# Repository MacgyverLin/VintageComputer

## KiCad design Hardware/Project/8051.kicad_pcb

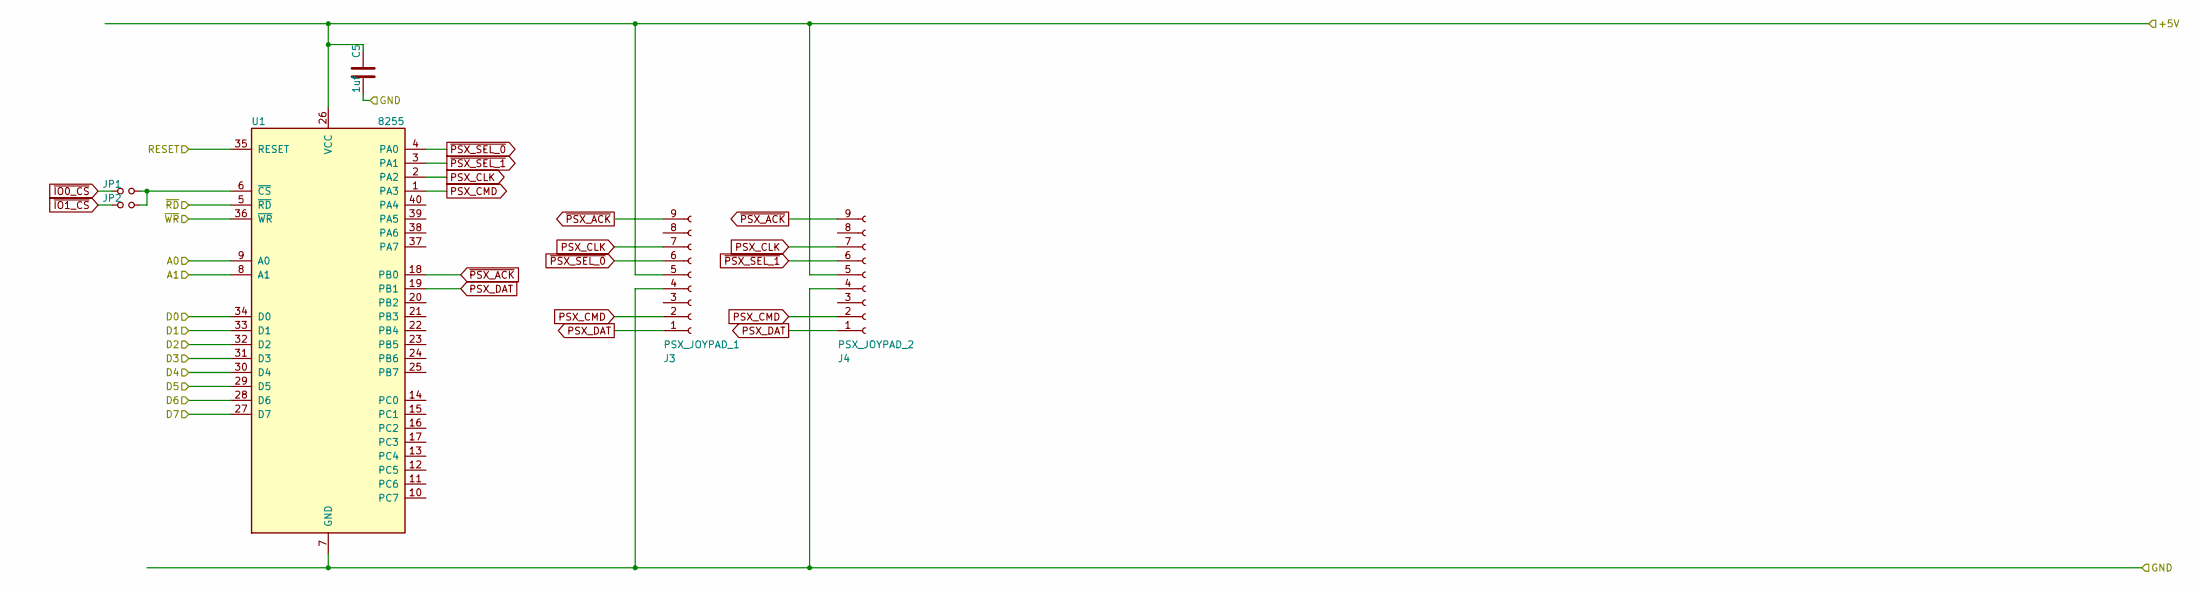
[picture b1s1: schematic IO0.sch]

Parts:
C5: 1uf; C_0805_2012Metric
J3: PSX_JOYPAD_1; PinSocket_1x09_P2.54mm_Vertical
J4: PSX_JOYPAD_2; PinSocket_1x09_P2.54mm_Vertical
JP1, JP2: SolderJumper-2_P1.3mm_Open_RoundedPad1.0x1.5mm
U1: 8255; DIP-40_W15.24mm

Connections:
/+5V: C5.1, J3.5, J4.5, U1.26 (VCC); also elsewhere on the board
/GND: C5.2, J3.4, J4.4, U1.7 (GND); also elsewhere on the board
/RESET: U1.35 (RESET); also elsewhere on the board
/~A0: U1.9 (A0); also elsewhere on the board
/~A1: U1.8 (A1); also elsewhere on the board
/~D0: U1.34 (D0); also elsewhere on the board
/~D1: U1.33 (D1); also elsewhere on the board
/~D2: U1.32 (D2); also elsewhere on the board
/~D3: U1.31 (D3); also elsewhere on the board
/~D4: U1.30 (D4); also elsewhere on the board
/~D5: U1.29 (D5); also elsewhere on the board
/~D6: U1.28 (D6); also elsewhere on the board
/~D7: U1.27 (D7); also elsewhere on the board
/~RD: U1.5 (~RD~); also elsewhere on the board
/~WR: U1.36 (~WR~); also elsewhere on the board
unnamed: JP1.2, JP2.2, U1.6 (~CS~)
PSX_CLK: J3.7, J4.7, U1.2 (PA2)
PSX_CMD: J3.2, J4.2, U1.1 (PA3)
PSX_DAT: J3.1, J4.1, U1.19 (PB1)
~IO0_CS: JP1.1; also elsewhere on the board
~IO1_CS: JP2.1; also elsewhere on the board
~PSX_ACK: J3.9, J4.9, U1.18 (PB0)
~PSX_SEL_0: J3.6, U1.4 (PA0)
~PSX_SEL_1: J4.6, U1.3 (PA1)

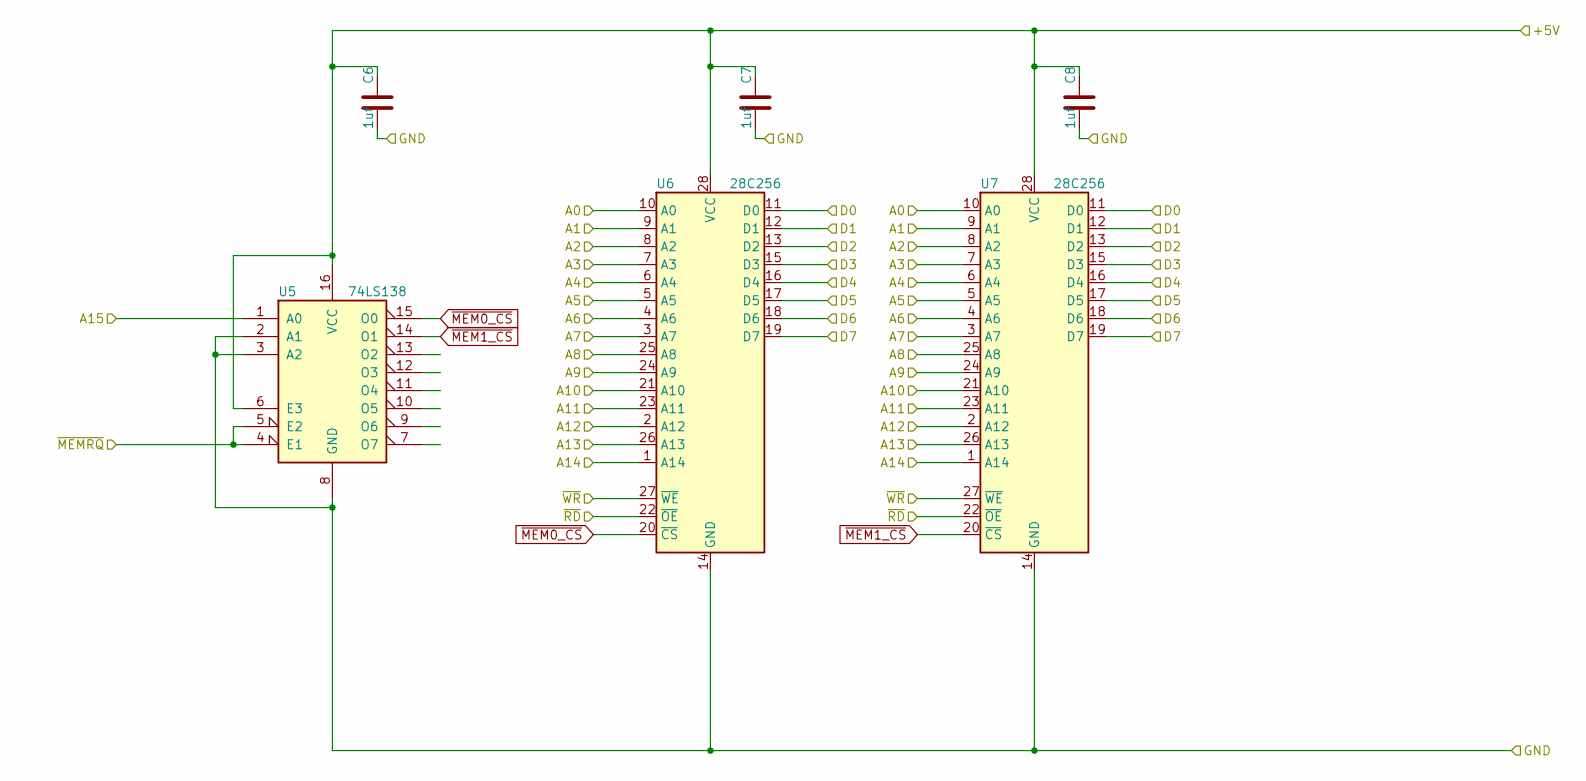
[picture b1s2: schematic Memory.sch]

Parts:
C6, C7, C8: 1uf; C_0805_2012Metric
U5: 74LS138; DIP-16_W7.62mm_Socket
U6, U7: 28C256; DIP-28_W15.24mm_Socket

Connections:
/+5V: C6.1, C7.1, C8.1, U5.6 (E3), U5.16 (VCC), U6.28 (VCC), U7.28 (VCC); also elsewhere on the board
/GND: C6.2, C7.2, C8.2, U5.2 (A1), U5.3 (A2), U5.8 (GND), U6.14 (GND), U7.14 (GND); also elsewhere on the board
/~A0: U6.10 (A0), U7.10 (A0); also elsewhere on the board
/~A1: U6.9 (A1), U7.9 (A1); also elsewhere on the board
/~A2: U6.8 (A2), U7.8 (A2); also elsewhere on the board
/~A3: U6.7 (A3), U7.7 (A3); also elsewhere on the board
/~A4: U6.6 (A4), U7.6 (A4); also elsewhere on the board
/~A5: U6.5 (A5), U7.5 (A5); also elsewhere on the board
/~A6: U6.4 (A6), U7.4 (A6); also elsewhere on the board
/~A7: U6.3 (A7), U7.3 (A7); also elsewhere on the board
/~A8: U6.25 (A8), U7.25 (A8); also elsewhere on the board
/~A9: U6.24 (A9), U7.24 (A9); also elsewhere on the board
/~A10: U6.21 (A10), U7.21 (A10); also elsewhere on the board
/~A11: U6.23 (A11), U7.23 (A11); also elsewhere on the board
/~A12: U6.2 (A12), U7.2 (A12); also elsewhere on the board
/~A13: U6.26 (A13), U7.26 (A13); also elsewhere on the board
/~A14: U6.1 (A14), U7.1 (A14); also elsewhere on the board
/~A15: U5.1 (A0); also elsewhere on the board
/~D0: U6.11 (D0), U7.11 (D0); also elsewhere on the board
/~D1: U6.12 (D1), U7.12 (D1); also elsewhere on the board
/~D2: U6.13 (D2), U7.13 (D2); also elsewhere on the board
/~D3: U6.15 (D3), U7.15 (D3); also elsewhere on the board
/~D4: U6.16 (D4), U7.16 (D4); also elsewhere on the board
/~D5: U6.17 (D5), U7.17 (D5); also elsewhere on the board
/~D6: U6.18 (D6), U7.18 (D6); also elsewhere on the board
/~D7: U6.19 (D7), U7.19 (D7); also elsewhere on the board
/~MEMRQ: U5.4 (E1), U5.5 (E2); also elsewhere on the board
/~RD: U6.22 (~OE), U7.22 (~OE); also elsewhere on the board
/~WR: U6.27 (~WE), U7.27 (~WE); also elsewhere on the board
~MEM0_CS: U5.15 (O0), U6.20 (~CS)
~MEM1_CS: U5.14 (O1), U7.20 (~CS)

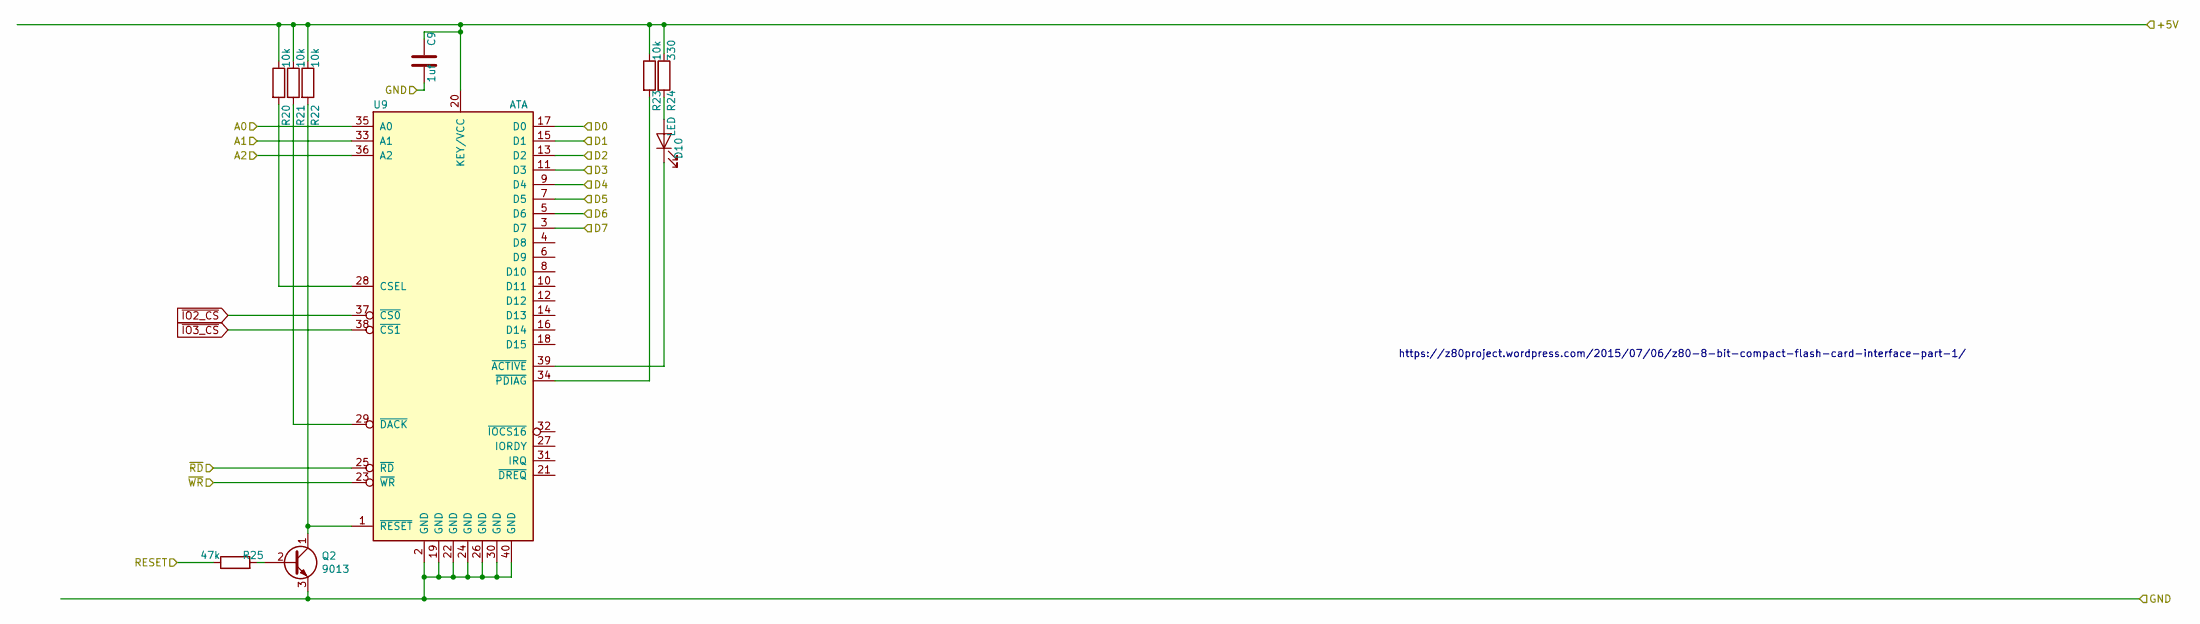
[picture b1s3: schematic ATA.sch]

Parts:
C9: 1uf; C_0805_2012Metric
D10: LED; LED_0805_2012Metric
Q2: 9013; TO-92
R20, R21, R22, R23: 10k; R_0805_2012Metric
R24: 330; R_0805_2012Metric
R25: 47k; R_0805_2012Metric
U9: ATA; PinHeader_2x20_P2.54mm_Vertical

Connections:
/+5V: C9.1, R20.1, R21.1, R22.1, R23.1, R24.1, U9.20 (KEY/VCC); also elsewhere on the board
/GND: C9.2, Q2.3 (E), U9.2 (GND), U9.19 (GND), U9.22 (GND), U9.24 (GND), U9.26 (GND), U9.30 (GND), U9.40 (GND); also elsewhere on the board
/RESET: R25.1; also elsewhere on the board
/~A0: U9.35 (A0); also elsewhere on the board
/~A1: U9.33 (A1); also elsewhere on the board
/~A2: U9.36 (A2); also elsewhere on the board
/~D0: U9.17 (D0); also elsewhere on the board
/~D1: U9.15 (D1); also elsewhere on the board
/~D2: U9.13 (D2); also elsewhere on the board
/~D3: U9.11 (D3); also elsewhere on the board
/~D4: U9.9 (D4); also elsewhere on the board
/~D5: U9.7 (D5); also elsewhere on the board
/~D6: U9.5 (D6); also elsewhere on the board
/~D7: U9.3 (D7); also elsewhere on the board
/~RD: U9.25 (~RD); also elsewhere on the board
/~WR: U9.23 (~WR); also elsewhere on the board
unnamed: D10.1 (K), U9.39 (~ACTIVE)
unnamed: D10.2 (A), R24.2
unnamed: Q2.1 (C), R22.2, U9.1 (~RESET~)
unnamed: Q2.2 (B), R25.2
unnamed: R20.2, U9.28 (CSEL)
unnamed: R21.2, U9.29 (~DACK)
unnamed: R23.2, U9.34 (~PDIAG)
~IO2_CS: U9.37 (~CS0); also elsewhere on the board
~IO3_CS: U9.38 (~CS1); also elsewhere on the board

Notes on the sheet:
https://z80project.wordpress.com/2015/07/06/z80-8-bit-compact-flash-card-interface-part-1/

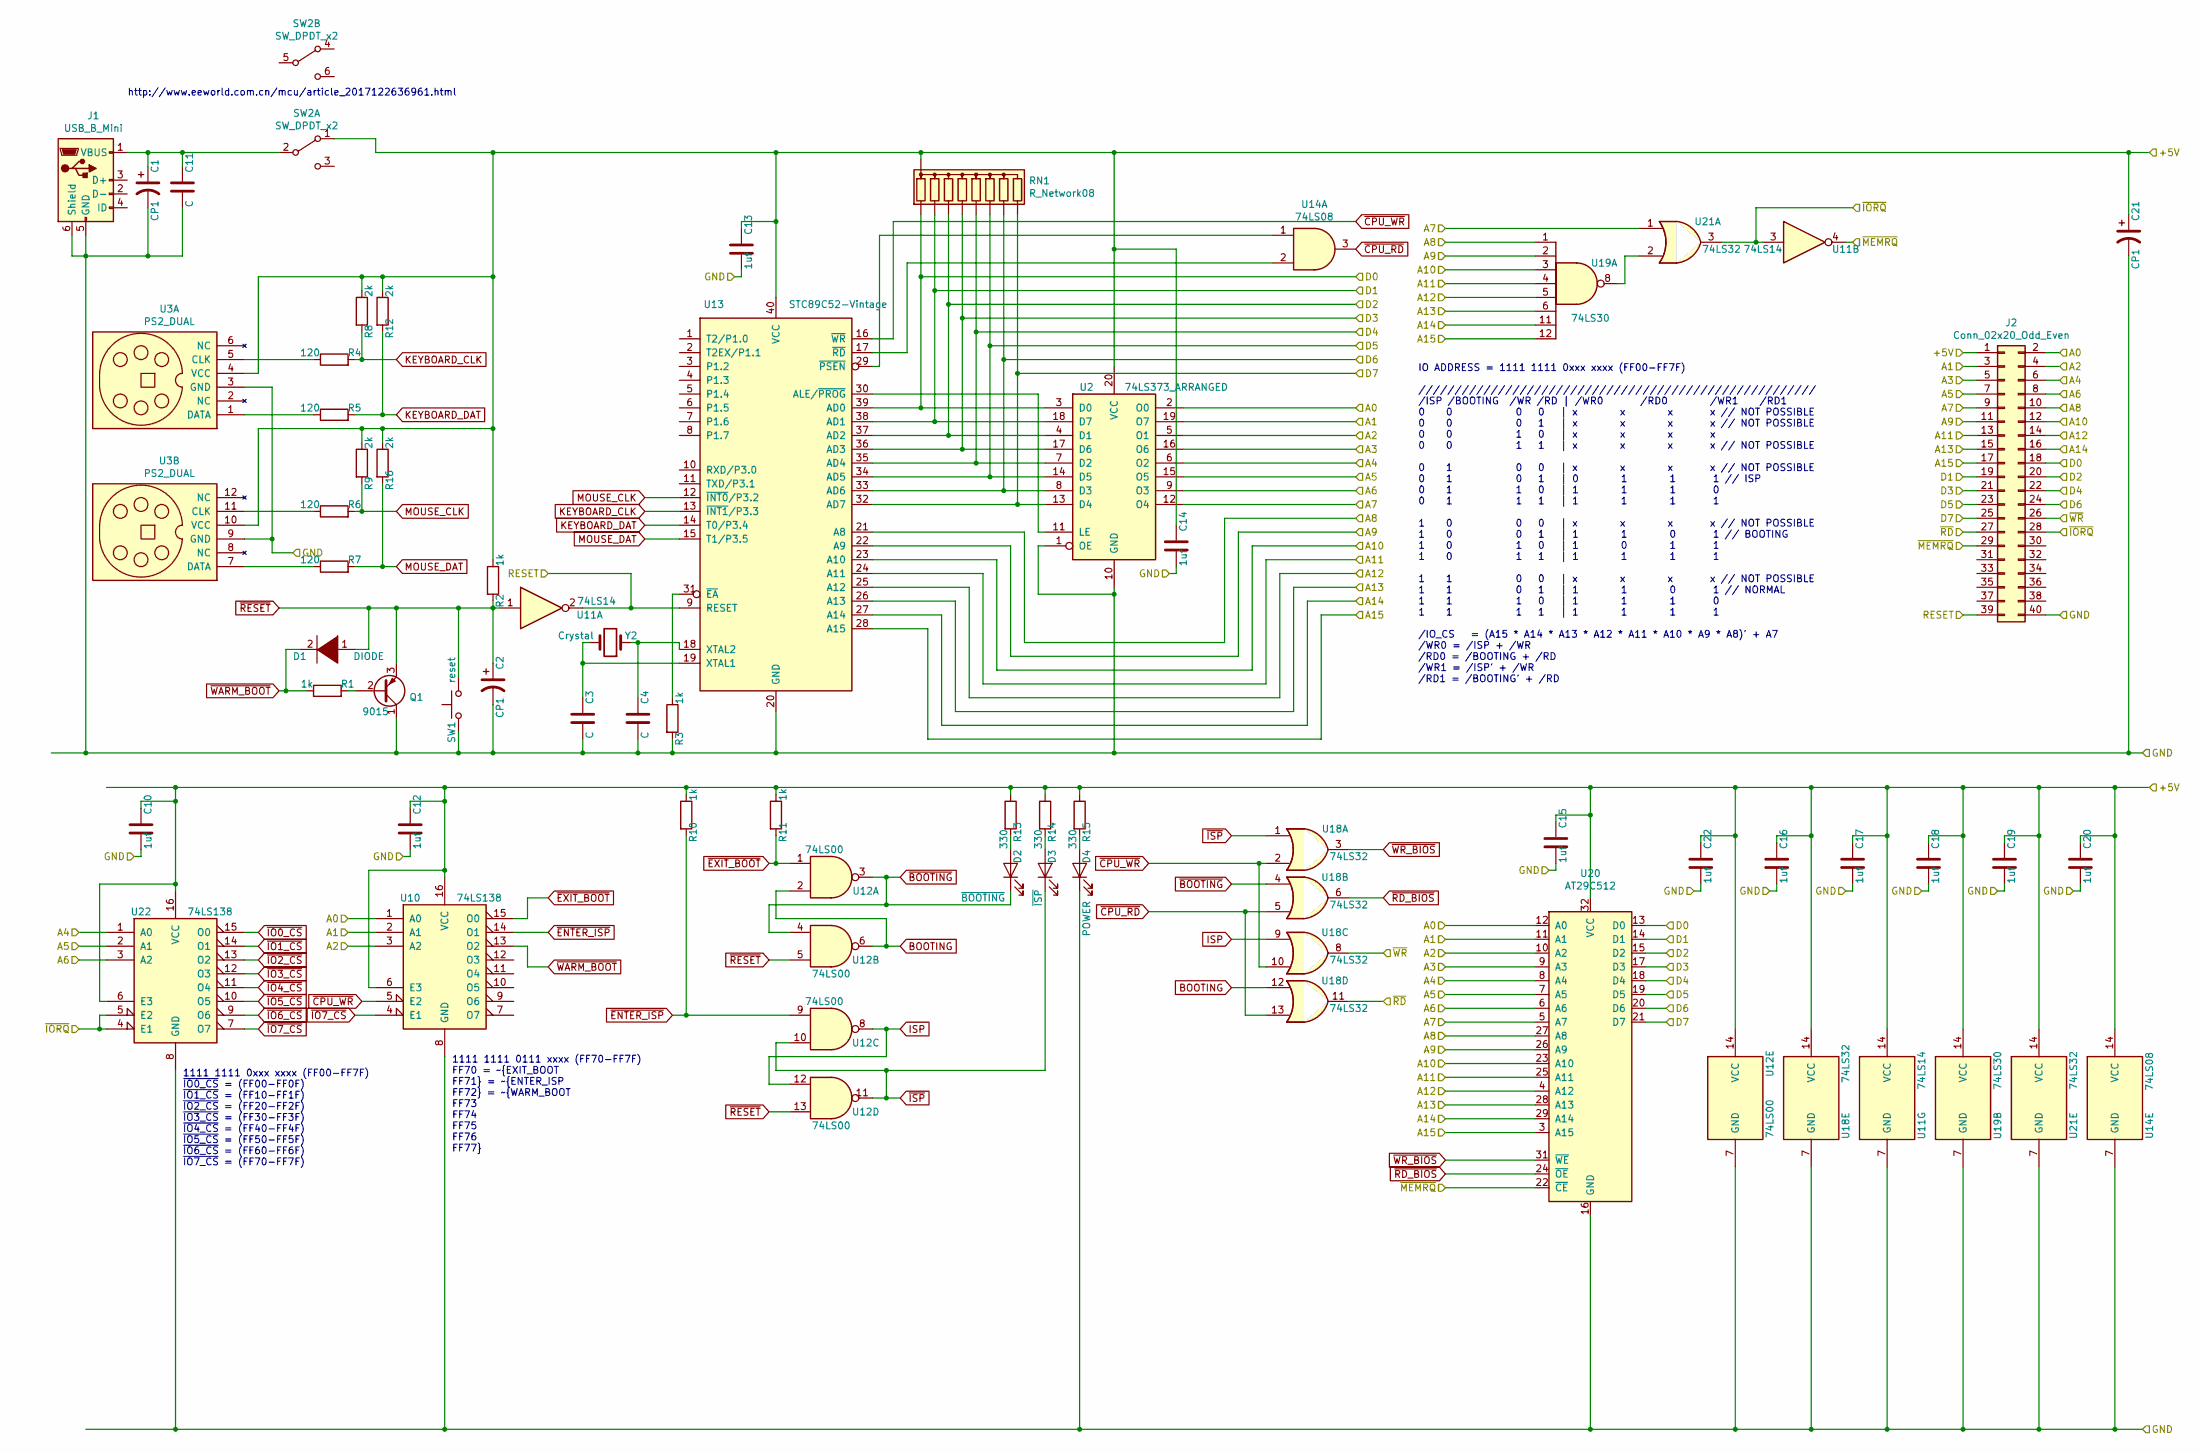
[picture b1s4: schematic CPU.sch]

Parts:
C1, C2, C21: CP1; CP_Radial_D7.5mm_P2.50mm
C3, C4, C11: C; C_0805_2012Metric
C10, C12, C13, C14, C15, C16, C17, C18, C19, C20, C22: 1uf; C_0805_2012Metric
D1: DIODE; LED_0805_2012Metric
D2: ~BOOTING; LED_0805_2012Metric
D3: ~ISP; LED_0805_2012Metric
D4: POWER; LED_0805_2012Metric
J1: USB_B_Mini; USB_Micro-B_Wuerth_629105150521_CircularHoles
J2: Conn_02x20_Odd_Even; PinHeader_2x20_P2.54mm_Vertical
Q1: 9015; TO-92
R1, R2, R3, R10, R11: 1k; R_0805_2012Metric
R4, R5, R6, R7: 120; R_0805_2012Metric
R8, R9, R12, R16: 2k; R_0805_2012Metric
R13, R14, R15: 330; R_0805_2012Metric
RN1: R_Network08; R_Array_SIP9
SW1: reset; SW_PUSH_6mm
SW2: SW_DPDT_x2; DIP-6_W7.62mm
U2: 74LS373_ARRANGED; DIP-20_W7.62mm_Socket
U3: PS2_DUAL; PS2DUAL
U10, U22: 74LS138; DIP-16_W7.62mm_Socket
U11: 74LS14; DIP-14_W7.62mm_Socket
U12: 74LS00; DIP-14_W7.62mm_Socket
U13: STC89C52-Vintage; DIP-40_W15.24mm_Socket
U14: 74LS08; DIP-14_W7.62mm_Socket
U18, U21: 74LS32; DIP-14_W7.62mm_Socket
U19: 74LS30; DIP-14_W7.62mm_Socket
U20: AT29C512; DIP-32_W15.24mm_Socket
Y2: Crystal; Crystal_HC18-U_Vertical

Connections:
/+5V: C10.1, C12.1, C13.1, C14.1, C15.1, C16.1, C17.1, C18.1, C19.1, C20.1, C21.1, C22.1, J2.1, R2.1, R8.1, R9.1, R10.1, R11.1, R12.1, R13.1, R14.1, R15.1, R16.1, RN1.1 (common), SW2.1 (A), U2.20 (VCC), U3.4 (VCC), U3.10 (VCC), U10.6 (E3), U10.16 (VCC), U11.14 (VCC), U12.14 (VCC), U13.40 (VCC), U14.14 (VCC), U18.14 (VCC), U19.14 (VCC), U20.32 (VCC), U21.14 (VCC), U22.6 (E3), U22.16 (VCC); also elsewhere on the board
/GND: C1.2, C2.2, C3.2, C4.2, C10.2, C11.2, C12.2, C13.2, C14.2, C15.2, C16.2, C17.2, C18.2, C19.2, C20.2, C21.2, C22.2, D4.1 (K), J1.5 (GND), J1.6 (Shield), J2.40, Q1.1 (C), R3.2, SW1.1, U2.1 (OE), U2.10 (GND), U3.3 (GND), U3.9 (GND), U10.8 (GND), U11.7 (GND), U12.7 (GND), U13.20 (GND), U14.7 (GND), U18.7 (GND), U19.7 (GND), U20.16 (GND), U21.7 (GND), U22.8 (GND); also elsewhere on the board
/RESET: J2.39, U11.2, U13.9 (RESET); also elsewhere on the board
/~A0: J2.2, U2.2 (O0), U10.1 (A0), U20.12 (A0); also elsewhere on the board
/~A1: J2.3, U2.19 (O7), U10.2 (A1), U20.11 (A1); also elsewhere on the board
/~A2: J2.4, U2.5 (O1), U10.3 (A2), U20.10 (A2); also elsewhere on the board
/~A3: J2.5, U2.16 (O6), U20.9 (A3); also elsewhere on the board
/~A4: J2.6, U2.6 (O2), U20.8 (A4), U22.1 (A0); also elsewhere on the board
/~A5: J2.7, U2.15 (O5), U20.7 (A5), U22.2 (A1); also elsewhere on the board
/~A6: J2.8, U2.9 (O3), U20.6 (A6), U22.3 (A2); also elsewhere on the board
/~A7: J2.9, U2.12 (O4), U20.5 (A7), U21.1; also elsewhere on the board
/~A8: J2.10, U13.21 (A8), U19.1, U20.27 (A8); also elsewhere on the board
/~A9: J2.11, U13.22 (A9), U19.2, U20.26 (A9); also elsewhere on the board
/~A10: J2.12, U13.23 (A10), U19.3, U20.23 (A10); also elsewhere on the board
/~A11: J2.13, U13.24 (A11), U19.4, U20.25 (A11); also elsewhere on the board
/~A12: J2.14, U13.25 (A12), U19.5, U20.4 (A12); also elsewhere on the board
/~A13: J2.15, U13.26 (A13), U19.6, U20.28 (A13); also elsewhere on the board
/~A14: J2.16, U13.27 (A14), U19.11, U20.29 (A14); also elsewhere on the board
/~A15: J2.17, U13.28 (A15), U19.12, U20.3 (A15); also elsewhere on the board
/~D0: J2.18, RN1.2 (R1), U2.3 (D0), U13.39 (AD0), U20.13 (D0); also elsewhere on the board
/~D1: J2.19, RN1.3 (R2), U2.18 (D7), U13.38 (AD1), U20.14 (D1); also elsewhere on the board
/~D2: J2.20, RN1.4 (R3), U2.4 (D1), U13.37 (AD2), U20.15 (D2); also elsewhere on the board
/~D3: J2.21, RN1.5 (R4), U2.17 (D6), U13.36 (AD3), U20.17 (D3); also elsewhere on the board
/~D4: J2.22, RN1.6 (R5), U2.7 (D2), U13.35 (AD4), U20.18 (D4); also elsewhere on the board
/~D5: J2.23, RN1.7 (R6), U2.14 (D5), U13.34 (AD5), U20.19 (D5); also elsewhere on the board
/~D6: J2.24, RN1.8 (R7), U2.8 (D3), U13.33 (AD6), U20.20 (D6); also elsewhere on the board
/~D7: J2.25, RN1.9 (R8), U2.13 (D4), U13.32 (AD7), U20.21 (D7); also elsewhere on the board
/~IORQ: J2.28, U11.3, U21.3, U22.4 (E1), U22.5 (E2)
/~MEMRQ: J2.29, U11.4, U20.22 (~CE); also elsewhere on the board
/~RD: J2.27, U18.11; also elsewhere on the board
/~WR: J2.26, U18.8; also elsewhere on the board
BOOTING: U12.2, U12.6, U18.12
ISP: U12.8, U12.12, U18.9
KEYBOARD_CLK: R4.2, R8.2, U13.13 (~INT1~/P3.3)
KEYBOARD_DAT: R5.2, R12.2, U13.14 (T0/P3.4)
MOUSE_CLK: R6.2, R9.2, U13.12 (~INT0~/P3.2)
MOUSE_DAT: R7.2, R16.2, U13.15 (T1/P3.5)
unnamed: C1.1, C11.1, J1.1 (VBUS), SW2.2 (B)
unnamed: C3.1, U13.19 (XTAL1), Y2.2
unnamed: C4.1, U13.18 (XTAL2), Y2.1
unnamed: D2.2 (A), R13.2
unnamed: D3.2 (A), R14.2
unnamed: D4.2 (A), R15.2
unnamed: Q1.2 (B), R1.2
unnamed: R3.1, U13.31 (~EA~)
unnamed: R4.1, U3.5 (CLK)
unnamed: R5.1, U3.1 (DATA)
unnamed: R6.1, U3.11 (CLK)
unnamed: R7.1, U3.7 (DATA)
unnamed: U13.17 (~RD~), U14.2
unnamed: U13.29 (~PSEN~), U14.1
unnamed: U2.11 (LE), U13.30 (ALE/~PROG~)
unnamed: U19.8, U21.2
~BOOTING: D2.1 (K), U12.3, U12.4, U18.4
~CPU_RD: U14.3, U18.5, U18.13
~CPU_WR: U10.5 (E2), U13.16 (~WR~), U18.2, U18.10
~ENTER_ISP: R10.2, U10.14 (O1), U12.9
~EXIT_BOOT: R11.2, U10.15 (O0), U12.1
~IO0_CS: U22.15 (O0); also elsewhere on the board
~IO1_CS: U22.14 (O1); also elsewhere on the board
~IO2_CS: U22.13 (O2); also elsewhere on the board
~IO3_CS: U22.12 (O3); also elsewhere on the board
~IO4_CS: U22.11 (O4)
~IO5_CS: U22.10 (O5)
~IO6_CS: U22.9 (O6)
~IO7_CS: U10.4 (E1), U22.7 (O7)
~ISP: D3.1 (K), U12.10, U12.11, U18.1
~RD_BIOS: U18.6, U20.24 (~OE)
~RESET: C2.1, D1.1 (K), Q1.3 (E), R2.2, SW1.2, U11.1, U12.5, U12.13
~WARM_BOOT: D1.2 (A), R1.1, U10.13 (O2)
~WR_BIOS: U18.3, U20.31 (~WE)

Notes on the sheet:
IO ADDRESS = 1111 1111 0xxx xxxx (FF00-FF7F) /////////////////////////////////////////////////////// /ISP /BOOTING /WR /RD | /WR0 /RD0 /WR1 /RD1 0 0 0 0 | x x x x // NOT POSSIBLE 0 0 0 1 | x x x x // NOT POSSIBLE 0 0 1 0 | x x x x 0 0 1 1 | x x x x // NOT POSSIBLE 0 1 0 0 | x x x x // NOT POSSIBLE 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
1111 1111 0111 xxxx (FF70-FF7F) FF70 = ~EXIT_BOOT FF71 = ~ENTER_ISP FF72 = ~WARM_BOOT FF73 FF74 FF75 FF76 FF77
1111 1111 0xxx xxxx (FF00-FF7F) ~IO0_CS~ = (FF00-FF0F) ~IO1_CS~ = (FF10-FF1F) ~IO2_CS~ = (FF20-FF2F) ~IO3_CS~ = (FF30-FF3F) ~IO4_CS~ = (FF40-FF4F) ~IO5_CS~ = (FF50-FF5F) ~IO6_CS~ = (FF60-FF6F) ~IO7_CS~ = (FF70-FF7F)
http://www.eeworld.com.cn/mcu/article_2017122636961.html

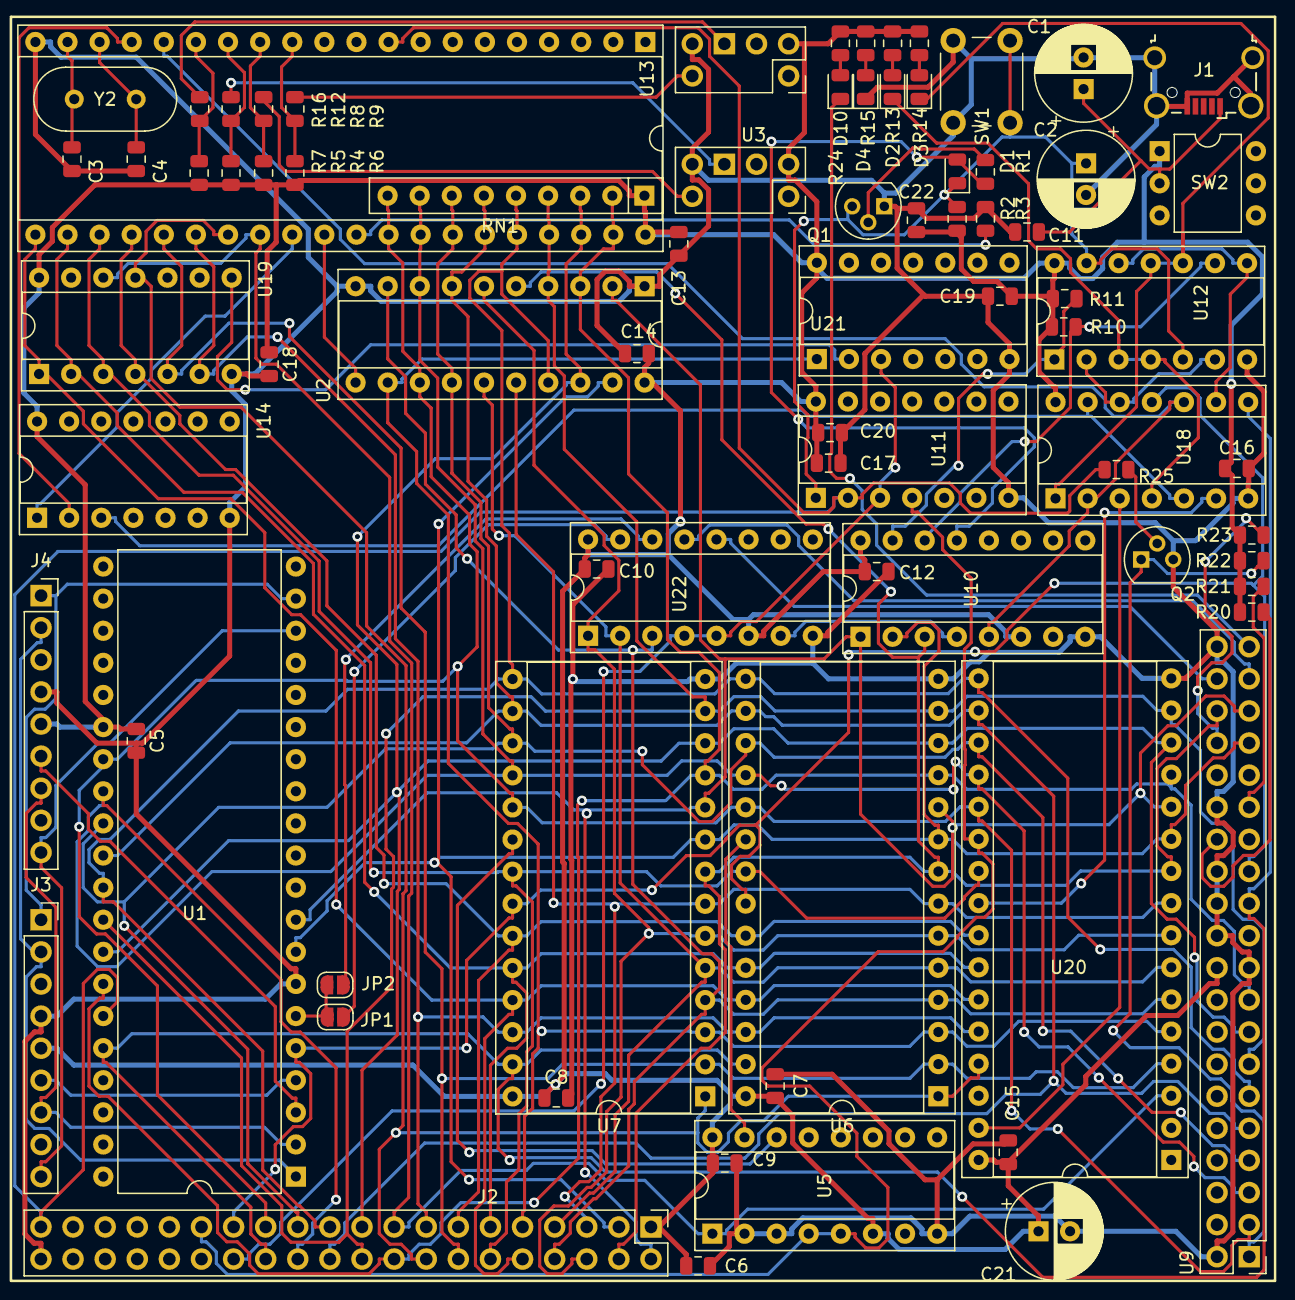
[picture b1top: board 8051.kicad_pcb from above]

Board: 2 copper layers, 78 parts (0 on the bottom side), 84 nets.
